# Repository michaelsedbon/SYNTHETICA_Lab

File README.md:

# SYNTHETICA Personal Lab

AI-assisted lab workspace for the SYNTHETICA project. Integrates with Notion (lab notebook + bibliography) and Airtable (reagents & labware inventory).

See the **[Cheat Sheet](file:///Users/michaelsedbon/Documents/SYNTHETIC_PERSONAL_LAB/CHEATSHEET.md)** for quick links to Notion and Airtable dashboards.

## Setup

### 1. Credentials

All credentials are stored in **`config.yaml`** (gitignored). Copy from the template:

```bash
cp .env.example .env   # Reference for required variables
```

The `config.yaml` file contains:
- **Notion Integration Token** — from [notion.so/my-integrations](https://www.notion.so/my-integrations)
- **Notion Database IDs** — Lab Notebook + Bibliography
- **Airtable Token** — from [airtable.com/create/tokens](https://airtable.com/create/tokens)
- **Airtable Base ID**

### 2. Python Dependencies

```bash
pip3 install requests pyyaml pymupdf
```

### 3. Notion Integration Sharing

Make sure the Notion integration is connected to both databases:
1. Open each database in Notion
2. Click "..." → "Connections" → Add your integration

## Usage

### Sync Bibliography (new papers)
```bash
python3 scripts/sync_bibliography.py        # Download new papers
python3 scripts/sync_bibliography.py --list  # List all papers
```

### Sync Experiments (new entries)
```bash
python3 scripts/sync_experiments.py          # Sync new experiments
python3 scripts/sync_experiments.py --list   # List all experiments
python3 scripts/sync_experiments.py --force  # Re-sync all
```

### Fetch Airtable Data
```bash
python3 scripts/fetch_airtable.py --test     # Test connection
python3 scripts/fetch_airtable.py Reagents   # Fetch reagents table
python3 scripts/fetch_airtable.py --all .    # Fetch all tables
```

### AI Assistant Workflows

When working with the AI assistant (Antigravity), use these commands:
- **`/catch-up`** — Sync everything and report what's new
- **`/sync-bibliography`** — Sync bibliography only
- **`/sync-experiments`** — Sync experiments only

## Project Structure

```
SYNTHETIC_PERSONAL_LAB/
├── .agent/                    # AI assistant config (MANIFEST, workflows, skills)
│   ├── MANIFEST.md            # Project memory — read every conversation
│   ├── conventions.md         # Rules for the AI assistant
│   ├── workflows/             # 9 slash-command workflows (/deploy, /catch-up, …)
│   └── skills/                # 3 extended skills (fetch-papers, explore-network, …)
├── applications/              # 7 web applications (see applications/INDEX.md)
│   ├── INDEX.md               # App registry with ports, stacks, and status
│   ├── fab-planner/           # Production planning (Next.js + Prisma + Three.js)
│   ├── adc24-dashboard/       # Electrophysiology dashboard (FastAPI + Next.js)
│   ├── experiment-viewer/     # Experiment notebook browser (FastAPI + Next.js)
│   ├── research-scout/        # Interdisciplinary research mapper (FastAPI + Next.js)
│   ├── plasmid-viewer/        # GenBank plasmid map viewer (FastAPI + Next.js)
│   ├── virtual-lab/           # 3D lab model with Airtable inventory (Three.js)
│   └── launcher/              # Central app dashboard (Next.js)
├── config.yaml                # API credentials (gitignored)
├── scripts/                   # Python sync & utility scripts (see scripts/README.md)
├── papers/                    # Downloaded reference PDFs (user's collection)
├── papers_txt/                # Plain-text extracts of user PDFs
│   └── INDEX.md               # Paper index for AI lookup
├── agent_papers/              # PDFs downloaded by AI assistant
├── agent_papers_txt/          # Text extracts of AI-downloaded papers
│   └── INDEX.md               # AI paper index
├── experiments/               # Per-experiment folders (see experiments/README.md)
│   ├── EXP_INDEX.md           # Experiment index for AI lookup
│   ├── EXPERIMENT_TEMPLATE.md # Template for new experiments
│   └── EXP_001…003/           # Individual experiment data
├── Project_space/             # Hardware design files & CAD assets
│   └── Cryptographic_beings/  # Motor controller PCB (KiCad, SKiDL)
├── Software/                  # Reference manuals & datasheets
├── CHEATSHEET.md              # Quick links to Notion & Airtable
├── SETUP_NEW_LAB.md           # Guide for cloning this scaffold
└── README.md                  # This file
```

## Deployment

The production server runs at `172.16.1.80` (SSH key auth, user `michael`, repo at `/opt/synthetica-lab/`). Use `/deploy` to commit, push, and pull on the server. See `.agent/workflows/deploy.md` for full details including service restart commands.

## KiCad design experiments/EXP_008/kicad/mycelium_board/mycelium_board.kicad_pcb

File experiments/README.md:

# Experiments

All lab experiments live under `experiments/`. Each experiment gets a sequential folder (`EXP_001`, `EXP_002`, …) containing standardised documentation and data files.

## Quick Start

| Action | Command |
|--------|---------|
| Create a new experiment | Use the AI assistant: `/create-experiment` |
| Sync experiments from Notion | `python3 scripts/sync_experiments.py` |
| Push local changes to Notion | `python3 scripts/push_experiment_to_notion.py EXP_XXX` |
| List all experiments | `python3 scripts/sync_experiments.py --list` |

## Folder Structure

Every experiment **must** contain these 4 files (see [EXPERIMENT_TEMPLATE.md](EXPERIMENT_TEMPLATE.md)):

```
experiments/EXP_XXX/
├── summary.md         # High-level overview, goals, status, results
├── LOG.md             # Chronological, append-only log of every action
├── SCRIPT_INDEX.md    # Index of scripts, firmware, data files
└── DOC_INDEX.md       # Index of all markdown/documentation files
```

Additional subdirectories are experiment-specific (e.g. `data/`, `figures/`, `model/`, `firmware/`, `hardware/`).

## Conventions

1. **Log everything** — every action, file creation, or change **must** be appended to `LOG.md` with a date heading (`## YYYY-MM-DD — Description`).
2. **Keep summary current** — after significant changes, update `summary.md`.
3. **Index new files** — scripts/data → `SCRIPT_INDEX.md`; markdown files → `DOC_INDEX.md`.
4. **Cross-link** — always use proper markdown links (`[REPORT.md](REPORT.md)`), never bare filenames.
5. **Sync to Notion** — after local updates, push with `python3 scripts/push_experiment_to_notion.py EXP_XXX`.

## Index

The master experiment index is [EXP_INDEX.md](EXP_INDEX.md) — a machine-readable list of all experiments with titles, dates, and one-line summaries. Updated automatically by sync scripts and the AI assistant.

## Current Experiments

| ID | Title | Status |
|----|-------|--------|
| EXP_001 | Growing *Pleurotus eryngii* | Active |
| EXP_002 | Cryptographic Beings — LLM Autonomous Control | Phase 2 |
| EXP_003 | Marimo Buoyancy Mathematical Modeling | Complete |

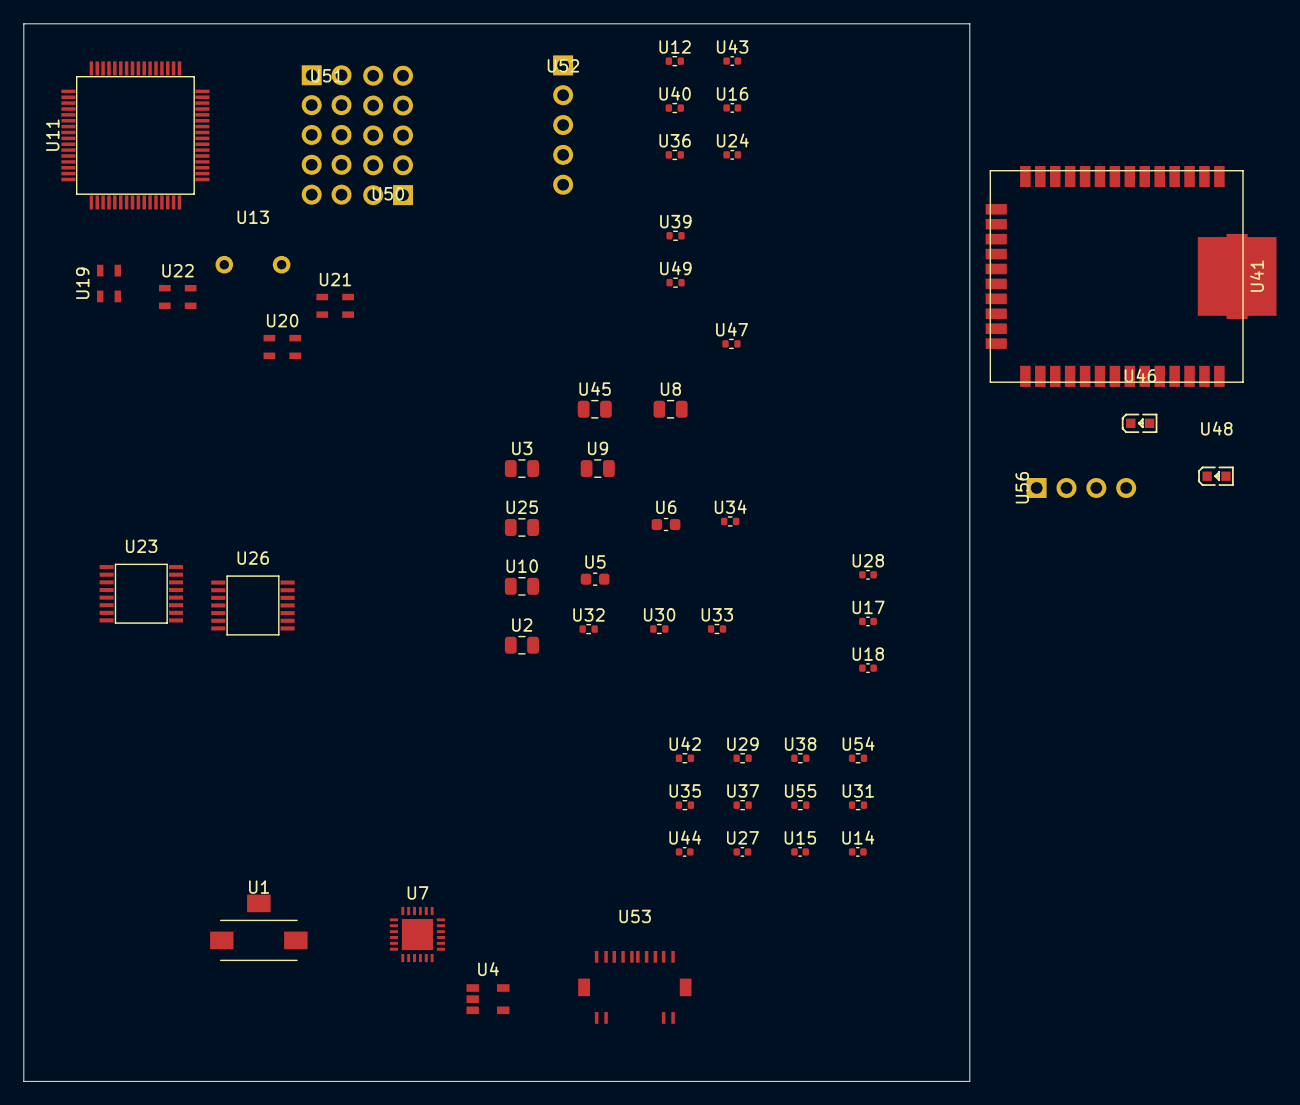
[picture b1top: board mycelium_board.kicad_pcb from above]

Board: 4 copper layers, 80.5 x 90.0 mm, 56 parts (0 on the bottom side), 66 nets, no tracks yet.

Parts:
U1: ?; SOT-223-3_L6.5-W3.4-H1.6-LS7.0-BR
U2, U3, U8, U9, U10, U25, U45: ?; C0805
U4: ?; SOT-23-5_L3.0-W1.7-H1.3-LS2.8-BR
U5, U6: ?; C0603
U7: ?; QFN-24_L4.0-W4.0-P0.5-BL-EP2.65
U11: ?; TQFP-64_L10.0-W10.0-P0.5-LS12.0-BL
U12, U29, U30, U31, U32, U33, U34, U35, U36, U37, U38, U39, U40, U42, U47, U49, U54, U55: ?; R0402
U13: ?; HC-49S_L11.0-W4.6
U14, U15, U16, U17, U18, U24, U27, U28, U43, U44: ?; C0402
U19, U20, U21, U22: ?; SOT-143B_L2.9-W1.3-H1.1-LS2.4-BR
U23: ?; TSSOP-16_L5.0-W4.4-P0.65-LS6.4-BL
U26: ?; TSSOP-14_L5.0-W4.4-P0.65-LS6.4-BL
U41: ?; WIFI-SMD_ESP32-S3-WROOM-1
U46, U48: ?; LED0603-RD
U50, U51: ?; HDR-TH_10P-P2.54-V-R2-C5
U52: ?; HDR-TH_5P-P2.54-V
U53: ?; USB-C-SMD-16P
U56: ?; HDR-TH_4P-P2.54-V

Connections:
avdd: U4.5, U6.1, U11.19, U11.48, U11.53, U11.61, U12.1, U16.1, U17.1, U18.1, U19.1, U20.1, U21.1, U22.1
biasout: U11.21, U11.23
cc1: U53.4, U54.1
cc2: U53.6, U55.1
clk: U11.50, U13.1, U14.1
cs: U11.3, U41.16
dout: U11.64, U41.17
drdy: U11.4, U41.7
dvdd: U1.2, U3.1, U7.1, U7.9, U8.1, U41.2, U42.1, U44.1, U45.1, U47.1, U56.1
en: U41.3, U42.2, U43.1
gnd: U1.1, U2.2, U3.2, U4.2, U5.2, U6.2, U7.13, U8.2, U9.2, U10.2, U11.7, U11.20, U11.49, U11.60, U14.2, U15.2, U16.2, U17.2, U18.2, U19.3, U20.3, U21.3, U22.3, U23.3, U23.7, U23.8, U23.9, U23.10, U24.2, U25.2, U27.2, U28.2, U41.41, U43.2, U44.2, U45.2, U46.1, U48.1, U50.9, U50.10, U51.9, U51.10, U52.5, U53.5, U54.2, U55.2, U56.4
gpio8: U41.14, U49.1
ina_n: U26.2, U29.1
ina_p: U26.3, U30.2
inb_n: U26.6, U32.1
inb_p: U26.5, U33.2
inc_n: U26.9, U35.1
inc_p: U26.10, U36.2
ind_n: U26.13, U38.1
ind_p: U26.12, U39.2
inn1: U11.13, U19.4, U50.2
inn2: U11.15, U20.4, U50.4
inn3: U11.17, U21.4, U50.6
inn4: U11.11, U22.4, U50.8
inn5: U11.58, U51.2
inn6: U11.56, U51.4
inn7: U11.54, U51.6
inn8: U11.9, U51.8
inp1: U11.12, U19.2, U50.1
inp2: U11.14, U20.2, U50.3
inp3: U11.16, U21.2, U50.5
inp4: U11.18, U22.2, U50.7
inp5: U11.57, U51.1
inp6: U11.59, U51.3
inp7: U11.55, U51.5
inp8: U11.10, U51.7
mcu.led_act-anode: U48.2, U49.2
mcu.led_pwr-anode: U46.2, U47.2
out1: U31.2, U52.1
out2: U34.2, U52.2
out3: U37.2, U52.3
out4: U40.2, U52.4
outa: U26.1, U29.2, U31.1
outb: U26.7, U32.2, U34.1
outc: U26.8, U35.2, U37.1
outd: U26.14, U38.2, U40.1
p2: U13.2, U15.1
pwdn: U11.51, U12.2
recording-din: U11.2, U41.19
recording-sclk: U11.1, U41.18
reset: U11.52, U41.9
start: U11.5, U41.8
stimulation-din: U23.4, U41.29
stimulation-sclk: U23.5, U41.28
swclk: U41.35, U56.3
swdio: U41.34, U56.2
sync: U23.6, U41.30
usb_dm: U41.38, U53.2
usb_dp: U41.39, U53.3
vin: U1.3, U2.1, U4.1, U4.3, U5.1, U53.1
vneg: U7.20, U10.1, U26.11, U28.1
vouta: U23.1, U30.1
voutb: U23.2, U33.1
voutc: U23.15, U36.1
voutd: U23.16, U39.1
vpos: U7.12, U9.1, U23.13, U23.14, U24.1, U25.1, U26.4, U27.1

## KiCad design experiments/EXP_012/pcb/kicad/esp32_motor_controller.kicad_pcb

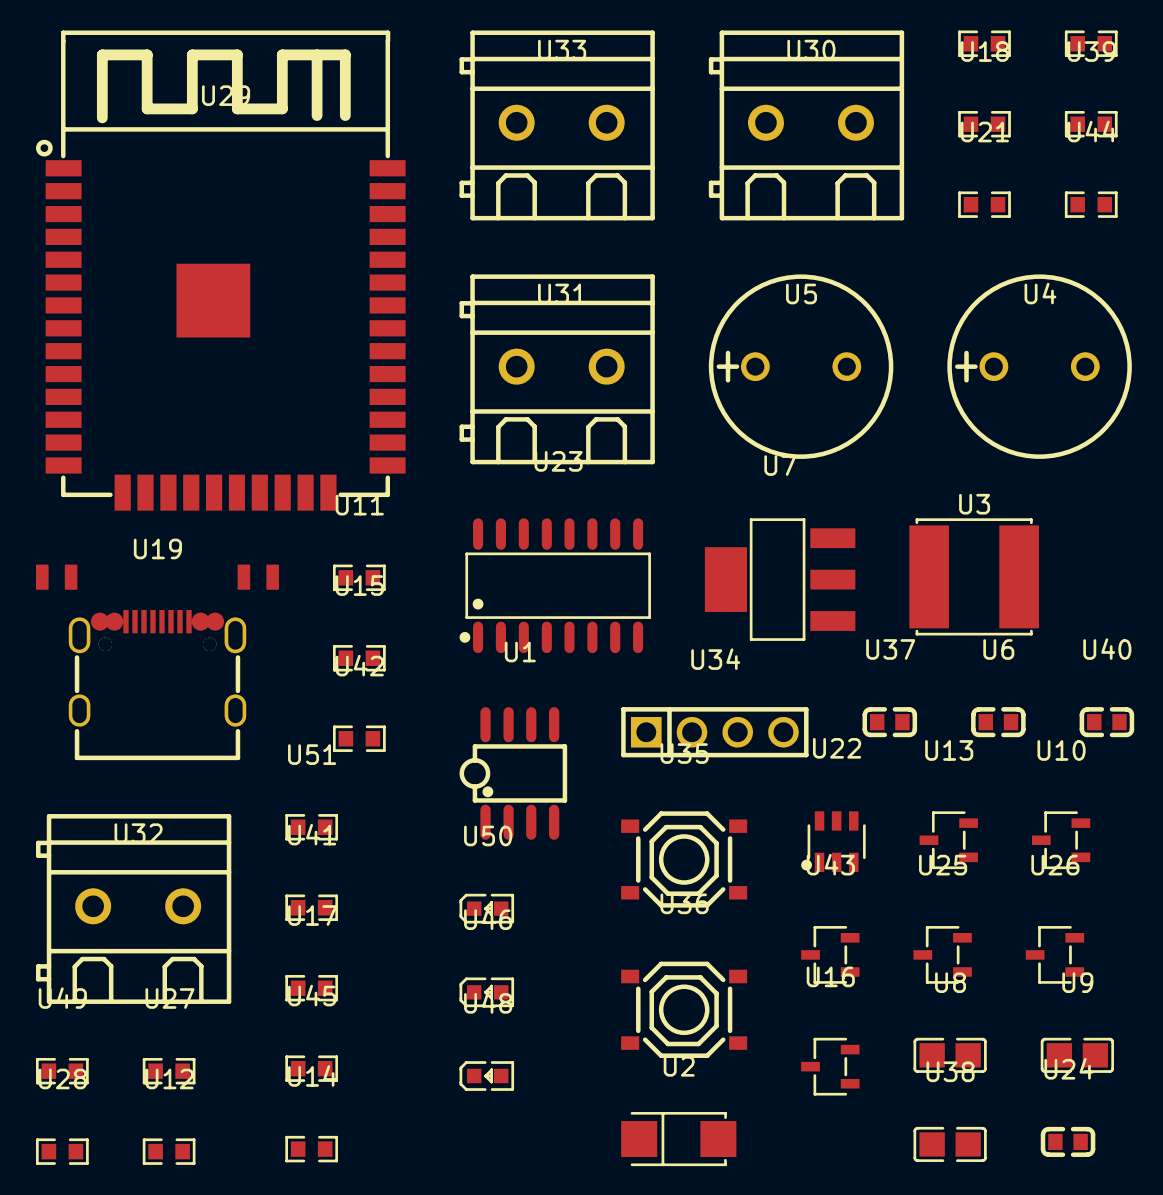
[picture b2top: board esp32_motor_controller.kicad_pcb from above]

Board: 2 copper layers, 51 parts (0 on the bottom side), 37 nets, no tracks yet.

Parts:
U1: ?; SOP-8_L4.9-W3.9-P1.27-LS6.0
U2: ?; SMA_L4.4-W2.8-LS5.4
U3: ?; IND-SMD_L6.6-W6.6
U4, U5: ?; CAP-SMD_BD6.3-L6.6-W6.6-LS7.6-FD
U6, U24, U37, U40: ?; C0603
U7: ?; SOT-223-3_L6.5-W3.4-H1.6-LS7.0-BR
U8, U9, U38: ?; C0805
U10, U13, U16, U25, U26: ?; SOT-23-3_L2.9-W1.6-H1.2-LS2.8-BR
U11, U12, U14, U15, U17, U18, U20, U21, U27, U28, U39, U41, U42, U44, U45, U47, U49, U51: ?; R0603
U19: ?; USB-C-SMD_TYPE-C-31-M-12
U22: ?; SOT-23-6_L2.9-W1.6-H1.2-LS2.8-BR
U23: ?; SOP-16_L10.0-W3.9-P1.27-LS6.0
U29: ?; WIFI-SMD_ESP32-WROOM-32
U30, U31, U32, U33: ?; CONN-TH_2P-P5.08_WJ128V-5.0-2P
U34: ?; HDR-TH_4P-P2.54-V
U35, U36: ?; SW-SMD_L5.1-W5.1-P3.70
U43: ?; SOD-323_L1.8-W1.3-LS2.5-RD
U46, U48, U50: ?; LED0603

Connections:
cc1: U19.A5, U20.1
cc2: U19.B5, U21.1
dir_in: U14.1, U29.28
dir_plus: U13.2, U15.2, U32.1
dm: U19.A7, U22.6
dp: U19.A6, U22.3
dtr: U23.13, U26.3, U27.1
ena_in: U17.1, U29.30
ena_plus: U16.2, U18.2, U32.2
esp_en: U26.2, U29.3, U36.1, U39.2, U40.1
esp_gpio0: U25.2, U29.25, U35.1
esp_rx: U23.9, U29.34
esp_tx: U23.8, U29.35
gnd: U1.6, U2.1, U4.2, U5.2, U6.2, U7.1, U8.2, U9.2, U10.3, U13.3, U16.3, U20.2, U21.2, U22.2, U23.1, U24.2, U29.1, U30.2, U31.2, U33.2, U34.1, U35.2, U36.2, U37.2, U38.2, U40.2, U43.1, U46.1, U48.1, U50.1
gpio21: U29.33, U34.3, U44.2
gpio22: U29.36, U34.4, U45.2
gpio23: U29.37, U49.1
gpio25: U29.10, U51.1
gpio34: U29.6, U41.2, U42.2, U43.2
io1_out: U22.4, U23.5
io2_out: U22.5, U23.6
led_motor-anode: U50.2, U51.2
led_pwr-anode: U46.2, U47.2
led_wifi-anode: U48.2, U49.2
motor.ls_dir.q-base: U13.1, U14.2
motor.ls_ena.q-base: U16.1, U17.2
motor.ls_step.q-base: U10.1, U11.2
out: U1.2, U2.2, U3.1
p1: U33.1, U41.1
pul_plus: U10.2, U12.2, U31.1
rts: U23.14, U25.3, U28.1
step_in: U11.1, U29.27
usb.q1-base: U25.1, U27.2
usb.q2-base: U26.1, U28.2
v3v3: U7.2, U9.1, U22.1, U23.4, U23.16, U24.1, U29.2, U34.2, U37.1, U38.1, U39.1, U42.1, U44.1, U45.1, U47.1
v5: U1.4, U3.2, U5.1, U7.3, U8.1, U12.1, U15.1, U18.1
vin_24v: U1.5, U1.8, U4.1, U6.1, U30.1

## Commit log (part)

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2026-02-19 Initial commit: lab workspace with ADC-24 dashboard, launcher, experiments, and papers
2026-02-19 [launcher] Fix card links to use runtime hostname instead of SSG localhost
2026-02-19 [adc24] Skip arch -x86_64 Rosetta wrapper on Linux (server is native x86_64)
2026-02-19 [experiment-viewer] Add experiment notebook viewer + launcher updates (stop button, experiment-viewer registration)
2026-02-20 Portability: add SETUP_NEW_LAB guide, fix launcher stop button for partial status
2026-02-20 Fix React key warning in experiment-viewer sidebar
2026-02-21 feat(experiment-viewer): embed interactive Plotly plots inline in markdown viewer
    Replace static PNG images with their interactive Plotly HTML counterparts.
    Pre-processes markdown to detect img+link pairs and renders iframes.
    All 14 plots in EXP_001 summary now display as interactive charts.
2026-02-24 docs: update README and CATCHUP with v2 features
2026-02-24 feat: add 5 new weird-science topics (xenobots, bioluminescence, organoid intelligence, living materials, genetic circuits)
2026-02-24 feat: seed papers from PhD folder projected onto niche map as diamond markers
2026-02-25 fix: gitignore settings.json (machine-specific paths)
2026-02-25 feat(plasmid-viewer): Geneious-style interactions + improved rendering
    - Scroll=rotate, Ctrl+scroll=zoom toward cursor (no drag)
    - Features as filled directional arrows (CDS/gene get arrowheads)
    - Labels outside ring with leader lines
    - Status bar showing cursor bp, nucleotide, feature name
    - Selection tooltip showing feature span in bp
    - Variable track thickness by feature type
2026-02-25 feat(plasmid-viewer): feature batch + 12-o'clock zoom + documentation
    Major changes:
    - Zoom redesign: smooth transition from circle-center to 12-o'clock anchor
    - When feature selected: rotate to 12 o'clock then zoom in
    - Complementary strand display at high zoom
    - Label collision avoidance (radial stacking)
    - Drag-select DNA range on backbone
2026-02-25 feat(plasmid-viewer): curved inline labels follow arc curvature
    Labels inside feature arcs now render character-by-character along
    the arc. Text auto-flips on the bottom half to stay upright/readable.
2026-02-25 feat(plasmid-viewer): multi-select, curved labels, text orientation fix
    Multi-select:
    - Ctrl/Cmd+click toggles multi-select in both plasmid & annotations
    - Bulk action toolbar in annotations tab with delete button
    - Delete/Backspace key deletes all selected features
    - page.tsx: multiSelectedIds Set state, handleBulkDelete
    Visual:
2026-02-25 fix(plasmid-viewer): nucleotide text direction uses viewport center angle
    uprightAngle now uses atan2(viewport_center - circle_center) to
    determine text flip direction at z>8, so all visible text faces
    consistently regardless of which part of the circle is in view.
2026-02-25 fix(plasmid-viewer): simplify text orientation - always upward at high zoom
2026-02-25 feat(plasmid-viewer): ORF-frame AA translation, backbone replaced by AA blocks
    - AA now translated from each CDS/gene/ORF feature's actual reading
    frame, not just frame 1 from position 0
    - White backbone line replaced by thin dim line at high zoom
    - Colored AA codon blocks serve as the backbone within ORFs
    - Stop codons now correctly correspond to the feature's reading frame
    - Outside of annotated ORFs: no AA overlay (clean backbone)
2026-02-26 experiment-viewer: collapsible child files, internal .md link navigation, improved sidebar labels
2026-02-26 feat(experiment-viewer): add Cmd+click go-to-definition in code panel
    - Cmd+click on function/class/variable names jumps to their definition
    - Regex-based definition search for Python, JS/TS, Go, Rust
    - Navigation stack with back button for jumping history
    - Blue flash highlight on target definition line
    - Visual hint: underline + pointer cursor when Cmd key is held
2026-02-26 feat(experiment-viewer): add right-click context menu on code links
    - 'Open in code panel' (default action)
    - 'Open in Antigravity' (launches vscode://file/path:line)
    - 'Copy file path' option
    - Auto-closes on click outside or Escape
2026-02-26 fix: use VS Code internal CLI with -r to reuse existing window
    Opens file in the already-open VS Code workspace instead of
    launching a new window
2026-02-27 feat(experiment-viewer): auto-detect code links, standalone viewer, plain text endpoint
    - Expand isCodeFileLink to detect relative code file links (not just file:/// protocol)
    - Add resolveRelativeCodeHref to resolve relative paths to absolute file:/// URLs
    - Fetch source directories on mount for path resolution
    - Add /code route with standalone VS Code-like code viewer page
    - Add /api/raw endpoint to serve code files as plain text
    - Context menu: 'Open as plain text' and 'Open in code viewer' options
2026-03-02 Add agent timeline viewer to experiment viewer (/agent route)
2026-03-02 Fix katex CSS import for server: move to JS-only import
2026-03-02 Install lucide-react across all apps
2026-03-02 Add Nano remote flashing: ESP reset endpoint + TCP bridge + STK500v1 flasher
2026-03-02 Fix send_command to return actual Nano response from log
2026-03-02 Update all docs: AccelStepper, correct wiring (D5=STP D4=DIR D3=HALL), ISD04 pinout
2026-03-02 Agent core: add auto-nudge mechanism to prevent early stopping
2026-03-02 Fix runaway self-prompting: simplify to nudge-once, stop if enough work done
2026-03-02 Persistent memory: AGENT_STATE.md + git auto-sync + self-updating agent
2026-03-02 Add null guards for group.children backward compat
2026-03-02 Keep lib dirs: let folder tree organize them instead of hiding
2026-03-02 [lab-agent] Add retrieval memory, experiment templates, scheduler, Telegram bot
    Features:
    - search_sessions tool: keyword search across past session JSONL logs
    - create_experiment tool: creates folder + 4 template files
    - scheduler.py: cron-like task runner (hourly status, daily summary)
    - telegram_bot.py: Telegram bridge via long-polling (no deps)
    - server/main.py: wires scheduler + Telegram, adds CRUD endpoints
2026-03-03 [experiment-viewer] Agent monitoring dashboard: status bar, scheduler tab, memory viewer
    - Status bar: shows 3 model badges (general/coder/gemini), planner + Telegram status, next scheduled task
    - Scheduler tab: list/toggle/add/delete cron tasks with interval picker
    - Memory tab: renders AGENT_STATE.md, highlights reflections in purple cards
    - Auto-refreshes status every 30s
2026-03-03 fix: DXF viewer bulge rendering + interactive laser-cut DXF export in Fusion script
2026-03-03 refactor: replace all emoji icons with Lucide React components
2026-03-03 feat: assembly export script + assembly stage in fab-planner
2026-03-03 feat(launcher): add Remote Access section for online apps
    - Add online-apps.json config with Experiment Viewer (Cloudflare Tunnel) and MoClo V3 (GitHub Pages)
    - Add OnlineAppInfo type to apps.ts
    - Add /api/online-apps route to serve config
    - Add RemoteAppCard component with provider badges (Cloudflare/GitHub Pages)
    - Add Remote Access section below local app grid in launcher
    - Update INDEX.md with Online Access documentation
2026-03-03 fix(lab-agent): always route through Gemini planner + block hazardous commands for scheduler tasks
    - Always use Plan-Execute-Reflect when Gemini is available (removes keyword gate)
    - Add source parameter to chat() for user/scheduler/telegram tagging
    - Block MOVE, HOME, STOP, SPEED, etc. for automated (scheduler/telegram) tasks
    - Block run_command and run_experiment_script for automated tasks
    - Blocked calls logged with ⛔ in timeline
    - Add incident report: 2026-03-03_agent_routing_incident.md
2026-03-03 docs(lab-agent): add full LLM reasoning trace to incident report
2026-03-04 feat: named positions (tube1-5, home, half, quarter) + GOTO/SET_OFFSET API
2026-03-04 [agent-presence] Bigger face (600px), much higher contrast
2026-03-04 [agent-presence] Add LLM I/O panel with smart JSON formatting and tabbed bottom view
2026-03-04 [agent-presence] Always-visible LLM I/O: side-by-side columns, no tabs
2026-03-05 EXP_005: web dashboard, sensor wiring, disable auto-cal, WebSocket fix
    - New motor control web dashboard at /
    - Proximity sensor (LJ8A3-2-Z/BX) wired to Nano D3
    - Disabled auto-calibration on Nano boot (manual mode)
    - WebSocket sanitizer: strip non-ASCII bytes before broadcast
    - OLED init sequence updated to match old working firmware
    - flash_nano.py timeout increased to 15s
2026-03-07 EXP_007: MyceliumBrain — comprehensive literature review & feasibility analysis
    - Added EXP_006: Fungal Electrophysiology Literature Review
    - Added EXP_007: MyceliumBrain research (600+ lines, 25 papers, inline citations)
    - DishBrain paradigm analysis
    - Fungal electrophysiology (8 sub-sections incl. Slayman 1976, Tohoku 2024, Adamatzky 2026)
    - EAP hydrogel Pong precedent, active matter theory
    - Shiitake memristors, mycorrhizal bio-electric bridges
2026-03-07 EXP_006: full model suite — network, photoreceptor, adaptation, music mapper, WebSocket server, mycelium-sim app
    - network_model.py: 50-node spatial network with gap junction coupling
    - photoreceptor.py: WC-1 blue-light kinetics (Hill function)
    - adaptation.py: spike-frequency adaptation + resource depletion
    - stimulation.py: optic fiber, flood light, electrical stim manager
    - music_mapper.py: bio→music mapping (spike features → MIDI/Web Audio)
    - server.py: WebSocket server streaming network state at 30fps
2026-03-08 fix: preview sidebar on right + rendered markdown
    - Fixed CSS grid layout with explicit column positions (sidebar=1, main=2, preview=3)
    - Added marked.js CDN for proper markdown rendering in preview panel
    - YAML frontmatter displayed in styled block, body rendered as HTML
    - Copy button copies raw markdown text for pasting
2026-03-09 Add Atopile→KiCad workflow tutorial
2026-03-09 Convert remaining applications to git submodules
2026-03-09 Document submodule setup in AGENT_STATE.md and INDEX.md
    - Added 'Applications = Git Submodules' section to persistent memory
    - Added IMPORTANT banner to applications/INDEX.md
    - Added LED-DRV8/LED-RING hardware reference to agent state
    - Future conversations will discover submodule rules on startup
2026-03-09 [EXP_010] Update docs: Phase 1+2 progress in summary, LOG, DOC_INDEX, SCRIPT_INDEX
2026-03-10 [launcher] Update submodule: nvm auto-source + port cleanup
2026-03-10 [adc24] Update submodule: Protocol Runner (Phase 2.5)
2026-03-10 [exp009+adc24] LED driver heartbeat → ADC backend auto-discovery
2026-03-10 Update adc24-dashboard submodule
2026-03-10 Fix crypto.randomUUID crash on HTTP: use portable uuid() everywhere
2026-03-10 Add interactive Jupyter notebook for EXP_010 analysis
2026-03-10 Document EXP_010 as completed infrastructure phase
2026-03-12 EXP_014: Phase 4C — tabbed dashboard, manual calibration, camera support
    - Flashed EXP_014 firmware to Nano (IDENTIFY/SENSOR/HOME commands)
    - Fixed platformio.ini: nanoatmega328, 57600 baud (old bootloader)
    - Added manual calibration: max_steps, level % slider, persistent to devices.yaml
    - Added tabbed dashboard: Motors / Cameras / Relays (Lucide icons)
    - Added ESP32-CAM device type with MJPEG stream/capture cards
    - Added ISD04 level motor support via ESP8266 HTTP proxy
2026-03-13 feat: surface LattePanda dashboard URL in knowledge base Quick Access tables
    - Added Quick Access section to structure.md with machine controller URL first
    - Added Quick Access section to summary.md for project overview
    - Updated software.md last updated date
2026-03-13 fix: ws_clients scoping bug in broadcast_ws (set augmented assignment)
2026-03-16 Add grant-tracker as submodule
2026-03-16 Update grant-tracker submodule: Esc shortcut for side panels
2026-03-16 Update grant-tracker submodule (NEW badge) + search-grants workflow
2026-03-16 Update grant-tracker: partner detail right panel
2026-03-16 Broader grant search: 5 new grants, scraper scripts, API reference, run log
2026-03-17 Add 6 larger institutional grants: Horizon Europe, NEB, CNAP, DRAC, DAC Paris
2026-03-20 Update launcher submodule — compact experiment rows
2026-03-23 feat: knowledge graph improvements — linking, filters, auto-tagging
    Backend (_build_graph):
    - Papers linked to projects via CATEGORY_PROJECT_MAP (explicit category→project mapping)
    - Apps linked to experiments via full-text EXP_XXX scanning
    - Paper↔experiment cross-referencing via title matching
    - App→project inference via transitive experiment links
    - PhD experiment IDs prefixed (PhD_EXP_001) to avoid namespace collisions
